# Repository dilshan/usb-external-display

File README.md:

# USB seven segment display module

This seven segment display module is specifically designed to work with *POS* systems and banking applications. Initially, this module is developed to work with PC based systems, and later it was modified to work with other platforms and applications.

To simplify the communication interface this unit emulates a *COM* port in the host terminal. Because of this feature, this module can work with many systems without having any additional device driver(s).

This display module is designed around *STM32F103CB* MCU. The firmware of this display unit operates with most of the *STM32F103C* series MCUs, which including *STM32F103C8T6* based Blue Pill board. 

This is [certified](https://certification.oshwa.org/lk000003.html) open source hardware project. All the design files, [documentation](https://github.com/dilshan/usb-external-display/wiki), firmware source code are available to download at the [project source repository](https://github.com/dilshan/usb-external-display/releases). All the content of this project are distributed under the terms of the following license:

-   Hardware License: [CC BY 4.0](https://creativecommons.org/licenses/by/4.0/)
-   Software License: [MIT](https://github.com/dilshan/usb-external-display/blob/master/LICENSE)
-   Documentation License: [CC BY 4.0](https://creativecommons.org/licenses/by/4.0/)

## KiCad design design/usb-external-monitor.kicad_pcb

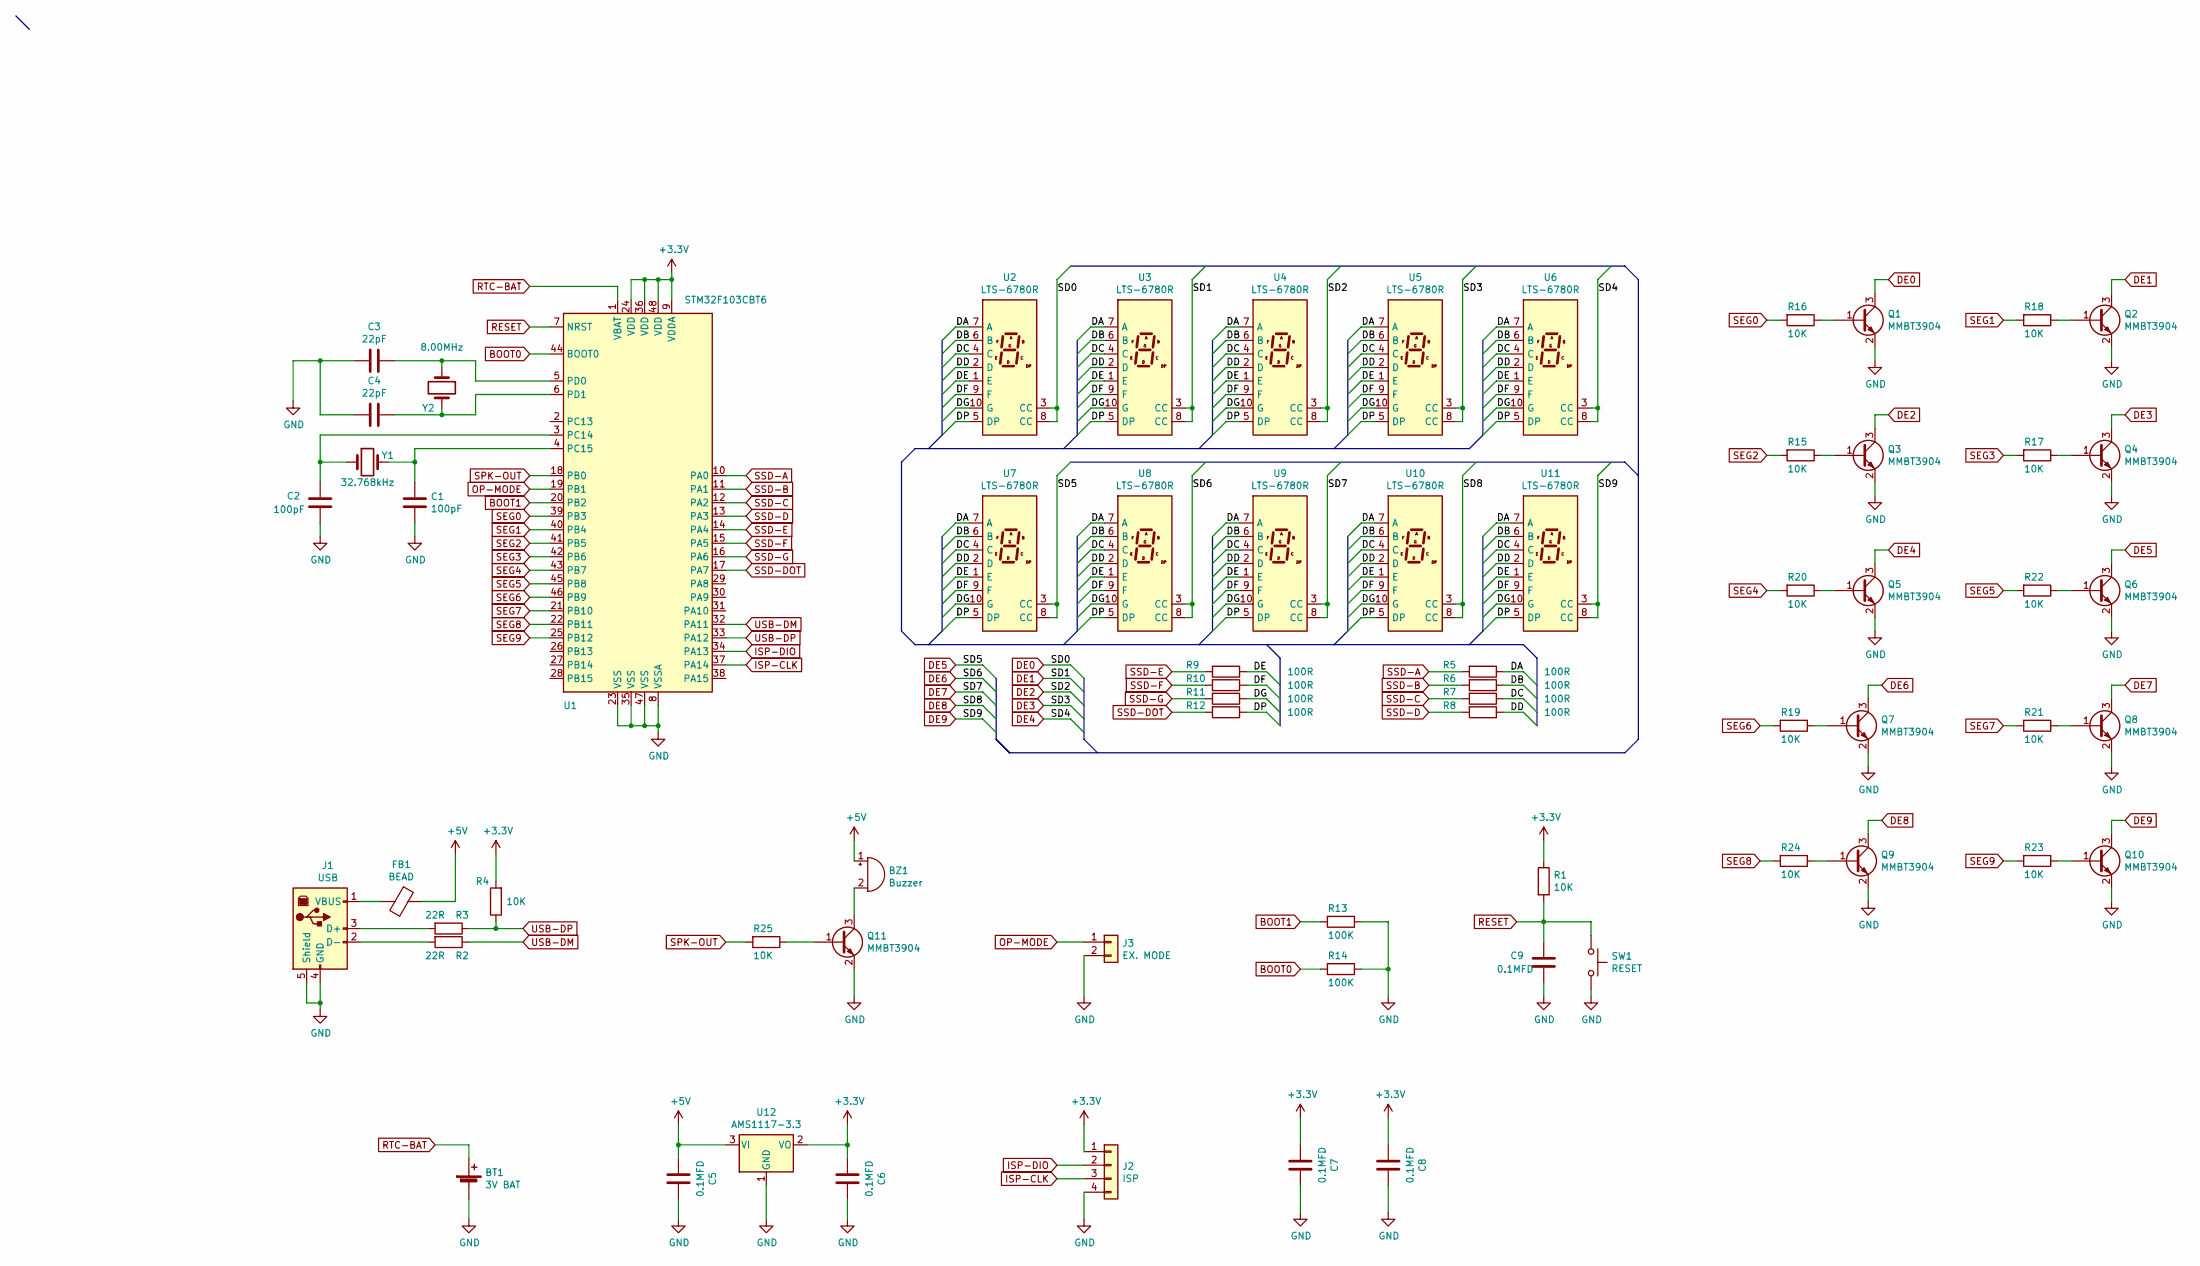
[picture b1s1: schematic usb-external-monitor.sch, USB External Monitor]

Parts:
BT1: 3V BAT; BatteryHolder_Keystone_105_1x2430
BZ1: Buzzer; Buzzer_12x9.5RM7.6
C1, C2: 100pF; C_0805_2012Metric
C3, C4: 22pF; C_0805_2012Metric
C5, C6, C7, C8, C9: 0.1MFD; C_0805_2012Metric
FB1: BEAD; L_Axial_L5.0mm_D3.6mm_P10.00mm_Horizontal_Murata_BL01RN1A2A2
J1: USB; USB_B_TE_5787834_Vertical
J2: ISP; PinHeader_1x04_P2.54mm_Vertical
J3: EX. MODE; PinHeader_1x02_P2.54mm_Vertical
Q1, Q2, Q3, Q4, Q5, Q6, Q7, Q8, Q9, Q10, Q11: MMBT3904; SOT-23
R1, R4, R15, R16, R17, R18, R19, R20, R21, R22, R23, R24, R25: 10K; R_0805_2012Metric
R2, R3: 22R; R_0805_2012Metric
R5, R6, R7, R8, R9, R10, R11, R12: 100R; R_0805_2012Metric
R13, R14: 100K; R_0805_2012Metric
SW1: RESET; SolderJumper-2_P1.3mm_Open_Pad1.0x1.5mm
U1: STM32F103CBT6; LQFP-48_7x7mm_P0.5mm
U2, U3, U4, U5, U6, U7, U8, U9, U10, U11: LTS-6780R; 7SegmentLED_LTS6760_LTS6780
U12: AMS1117-3.3; SOT-223-3_TabPin2
Y1: 32.768kHz; Crystal_C26-LF_D2.1mm_L6.5mm_Horizontal
Y2: 8.00MHz; Crystal_HC49-U_Vertical

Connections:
+3V3: C6.2, C7.2, C8.2, J2.1, R1.1, R4.2, U1.9 (VDDA), U1.24 (VDD), U1.36 (VDD), U1.48 (VDD), U12.2 (VO)
+5V: BZ1.1 (-), C5.2, FB1.1, U12.3 (VI)
/DA: R5.1, U2.7 (A), U3.7 (A), U4.7 (A), U5.7 (A), U6.7 (A), U7.7 (A), U8.7 (A), U9.7 (A), U10.7 (A), U11.7 (A)
/DB: R6.1, U2.6 (B), U3.6 (B), U4.6 (B), U5.6 (B), U6.6 (B), U7.6 (B), U8.6 (B), U9.6 (B), U10.6 (B), U11.6 (B)
/DC: R7.1, U2.4 (C), U3.4 (C), U4.4 (C), U5.4 (C), U6.4 (C), U7.4 (C), U8.4 (C), U9.4 (C), U10.4 (C), U11.4 (C)
/DD: R8.1, U2.2 (D), U3.2 (D), U4.2 (D), U5.2 (D), U6.2 (D), U7.2 (D), U8.2 (D), U9.2 (D), U10.2 (D), U11.2 (D)
/DE: R9.1, U2.1 (E), U3.1 (E), U4.1 (E), U5.1 (E), U6.1 (E), U7.1 (E), U8.1 (E), U9.1 (E), U10.1 (E), U11.1 (E)
/DF: R10.1, U2.9 (F), U3.9 (F), U4.9 (F), U5.9 (F), U6.9 (F), U7.9 (F), U8.9 (F), U9.9 (F), U10.9 (F), U11.9 (F)
/DG: R11.1, U2.10 (G), U3.10 (G), U4.10 (G), U5.10 (G), U6.10 (G), U7.10 (G), U8.10 (G), U9.10 (G), U10.10 (G), U11.10 (G)
/DP: R12.1, U2.5 (DP), U3.5 (DP), U4.5 (DP), U5.5 (DP), U6.5 (DP), U7.5 (DP), U8.5 (DP), U9.5 (DP), U10.5 (DP), U11.5 (DP)
BOOT0: R14.2, U1.44 (BOOT0)
BOOT1: R13.2, U1.20 (PB2)
DE0: Q1.3 (C), U2.3 (CC), U2.8 (CC)
DE1: Q2.3 (C), U3.3 (CC), U3.8 (CC)
DE2: Q3.3 (C), U4.3 (CC), U4.8 (CC)
DE3: Q4.3 (C), U5.3 (CC), U5.8 (CC)
DE4: Q5.3 (C), U6.3 (CC), U6.8 (CC)
DE5: Q6.3 (C), U7.3 (CC), U7.8 (CC)
DE6: Q7.3 (C), U8.3 (CC), U8.8 (CC)
DE7: Q8.3 (C), U9.3 (CC), U9.8 (CC)
DE8: Q9.3 (C), U10.3 (CC), U10.8 (CC)
DE9: Q10.3 (C), U11.3 (CC), U11.8 (CC)
GND: BT1.2 (-), C1.2, C2.2, C3.2, C4.2, C5.1, C6.1, C7.1, C8.1, C9.2, J1.4 (GND), J1.5 (Shield), J2.4, J3.2, Q1.2 (E), Q2.2 (E), Q3.2 (E), Q4.2 (E), Q5.2 (E), Q6.2 (E), Q7.2 (E), Q8.2 (E), Q9.2 (E), Q10.2 (E), Q11.2 (E), R13.1, R14.1, SW1.2, U1.8 (VSSA), U1.23 (VSS), U1.35 (VSS), U1.47 (VSS), U12.1 (GND)
ISP-CLK: J2.3, U1.37 (PA14)
ISP-DIO: J2.2, U1.34 (PA13)
unnamed: BZ1.2 (+), Q11.3 (C)
unnamed: C1.1, U1.4 (PC15), Y1.2
unnamed: C2.1, U1.3 (PC14), Y1.1
unnamed: C3.1, U1.5 (PD0), Y2.1
unnamed: C4.1, U1.6 (PD1), Y2.2
unnamed: FB1.2, J1.1 (VBUS)
unnamed: J1.2 (D-), R2.2
unnamed: J1.3 (D+), R3.2
unnamed: Q1.1 (B), R16.1
unnamed: Q2.1 (B), R18.1
unnamed: Q3.1 (B), R15.1
unnamed: Q4.1 (B), R17.1
unnamed: Q5.1 (B), R20.1
unnamed: Q6.1 (B), R22.1
unnamed: Q7.1 (B), R19.1
unnamed: Q8.1 (B), R21.1
unnamed: Q9.1 (B), R24.1
unnamed: Q10.1 (B), R23.1
unnamed: Q11.1 (B), R25.1
OP-MODE: J3.1, U1.19 (PB1)
RESET: C9.1, R1.2, SW1.1, U1.7 (NRST)
RTC-BAT: BT1.1 (+), U1.1 (VBAT)
SEG0: R16.2, U1.39 (PB3)
SEG1: R18.2, U1.40 (PB4)
SEG2: R15.2, U1.41 (PB5)
SEG3: R17.2, U1.42 (PB6)
SEG4: R20.2, U1.43 (PB7)
SEG5: R22.2, U1.45 (PB8)
SEG6: R19.2, U1.46 (PB9)
SEG7: R21.2, U1.21 (PB10)
SEG8: R24.2, U1.22 (PB11)
SEG9: R23.2, U1.25 (PB12)
SPK-OUT: R25.2, U1.18 (PB0)
SSD-A: R5.2, U1.10 (PA0)
SSD-B: R6.2, U1.11 (PA1)
SSD-C: R7.2, U1.12 (PA2)
SSD-D: R8.2, U1.13 (PA3)
SSD-DOT: R12.2, U1.17 (PA7)
SSD-E: R9.2, U1.14 (PA4)
SSD-F: R10.2, U1.15 (PA5)
SSD-G: R11.2, U1.16 (PA6)
USB-DM: R2.1, U1.32 (PA11)
USB-DP: R3.1, R4.1, U1.33 (PA12)

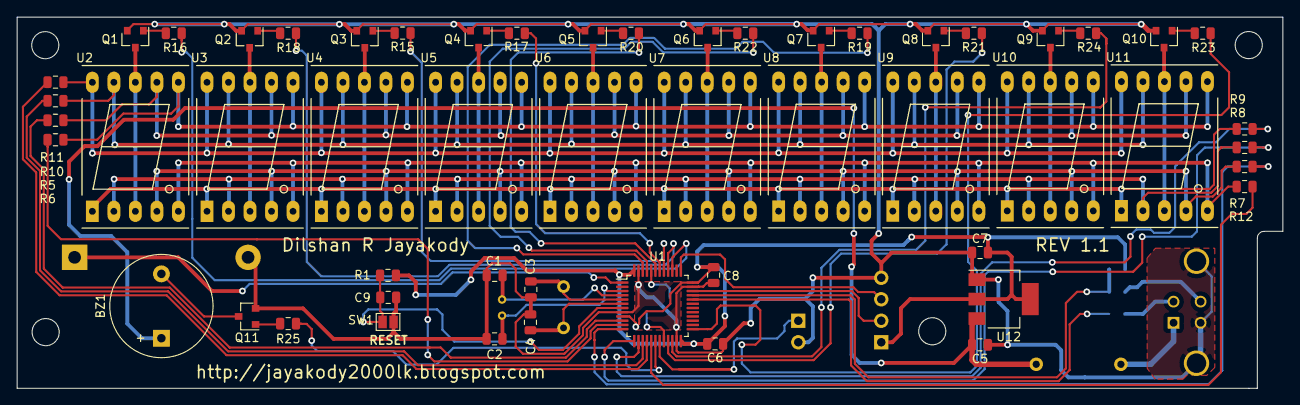
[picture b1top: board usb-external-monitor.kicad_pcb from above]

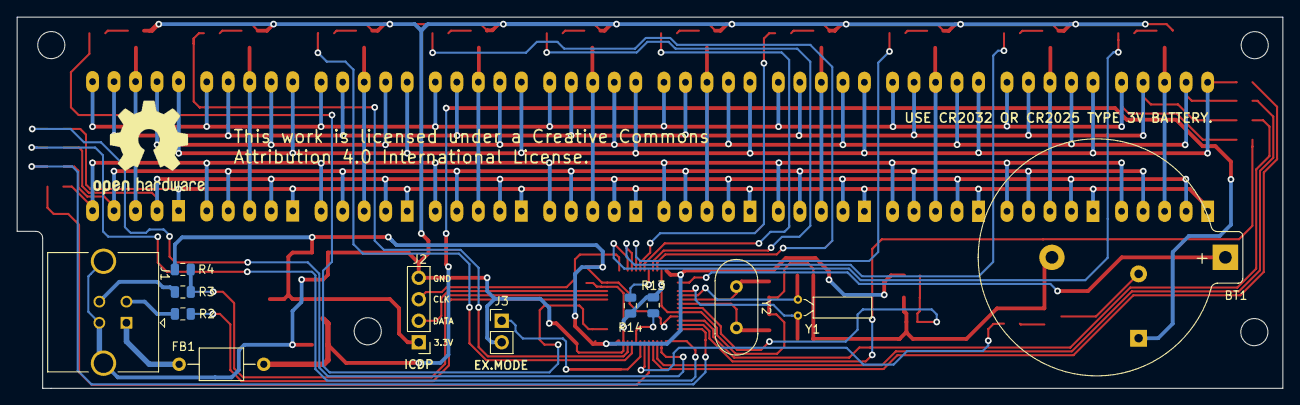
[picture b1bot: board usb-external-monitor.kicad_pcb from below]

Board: 2 copper layers, 149.5 x 43.8 mm, 70 parts (12 on the bottom side), 68 nets.

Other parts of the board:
 : MountingHole_3.2mm_M3
 #2,  #3,  #4: MountingHole_3.2mm_M3

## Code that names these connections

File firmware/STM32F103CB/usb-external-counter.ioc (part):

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Mcu.Name=STM32F103C(8-B)Tx
Mcu.Package=LQFP48
Mcu.UserName=STM32F103CBTx
PA0-WKUP.GPIOParameters=GPIO_Label
PA0-WKUP.GPIO_Label=SSD_A
PA0-WKUP.Signal=GPIO_Output
PA1.GPIOParameters=GPIO_Label
PA1.GPIO_Label=SSD_B
PA1.Signal=GPIO_Output
PA11.Mode=Device
PA11.Signal=USB_DM
PA12.Mode=Device
PA12.Signal=USB_DP
PA2.GPIOParameters=GPIO_Label
PA2.GPIO_Label=SSD_C
PA2.Signal=GPIO_Output
PA3.GPIOParameters=GPIO_Label
PA3.GPIO_Label=SSD_D
PA3.Signal=GPIO_Output
PA4.GPIOParameters=GPIO_Label
PA4.GPIO_Label=SSD_E
PA4.Signal=GPIO_Output
PA5.GPIOParameters=GPIO_Label
PA5.GPIO_Label=SSD_F
PA5.Signal=GPIO_Output
PA6.GPIOParameters=GPIO_Label
PA6.GPIO_Label=SSD_G
PA6.Signal=GPIO_Output
PA7.GPIOParameters=GPIO_Label
PA7.GPIO_Label=SSD_DOT
PA7.Signal=GPIO_Output
PB0.GPIOParameters=GPIO_Label
PB0.GPIO_Label=SPK_OUT
PB0.Signal=S_TIM3_CH3
PB1.GPIOParameters=GPIO_Label
PB1.GPIO_Label=OP_MODE
PB1.Signal=GPIO_Input
PB10.GPIOParameters=GPIO_Label
PB10.GPIO_Label=SSD_8
PB10.Signal=GPIO_Output
PB11.GPIOParameters=GPIO_Label
PB11.GPIO_Label=SSD_9
PB11.Signal=GPIO_Output
PB12.GPIOParameters=GPIO_Label
PB12.GPIO_Label=SSD_10
PB12.Signal=GPIO_Output
PB3.GPIOParameters=GPIO_Label
PB3.GPIO_Label=SSD_1
PB3.Signal=GPIO_Output
PB4.GPIOParameters=GPIO_Label
PB4.GPIO_Label=SSD_2
PB4.Signal=GPIO_Output
PB5.GPIOParameters=GPIO_Label
PB5.GPIO_Label=SSD_3
PB5.Signal=GPIO_Output
PB6.GPIOParameters=GPIO_Label
PB6.GPIO_Label=SSD_4
PB6.Signal=GPIO_Output
PB7.GPIOParameters=GPIO_Label
PB7.GPIO_Label=SSD_5
PB7.Signal=GPIO_Output
PB8.GPIOParameters=GPIO_Label
PB8.GPIO_Label=SSD_6
PB8.Signal=GPIO_Output
PB9.GPIOParameters=GPIO_Label
PB9.GPIO_Label=SSD_7
PB9.Signal=GPIO_Output
PC14-OSC32_IN.Mode=LSE-External-Oscillator
PC14-OSC32_IN.Signal=RCC_OSC32_IN
PC15-OSC32_OUT.Mode=LSE-External-Oscillator
PC15-OSC32_OUT.Signal=RCC_OSC32_OUT
PD0-OSC_IN.Mode=HSE-External-Oscillator
PD0-OSC_IN.Signal=RCC_OSC_IN
PD1-OSC_OUT.Mode=HSE-External-Oscillator
PD1-OSC_OUT.Signal=RCC_OSC_OUT
RCC.SYSCLKFreq_VALUE=48000000
RCC.SYSCLKSource=RCC_SYSCLKSOURCE_PLLCLK
board=custom

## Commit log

2019-06-29 Initial version of design files and firmware files.
2019-06-29 Update readme file with license information.
2019-06-29 Update readme file with image of the module.
2019-06-30 Update links in the readme file.
2019-06-30 Update readme file.
2019-07-08 Add OSHWA - LK000003 certificate information.

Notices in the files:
design/usb-external-monitor.kicad_pcb:
This work is licensed under a Creative Commons
Attribution 4.0 International License.
